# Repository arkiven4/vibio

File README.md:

This is a [Next.js](https://nextjs.org/) project bootstrapped with [`create-next-app`](https://github.com/vercel/next.js/tree/canary/packages/create-next-app).

## Build Apps

First, install necessary npm modules using command:

```sh
npm install
```

**TIPS:** In case if command failed, you can run that command again.

By default, the build target is x64 (x86_64) CPUs.
You can switch target using command (example for ARM32 chips):

```sh
sed -i 's#"nextron build -l"#"nextron build -l --armv7l"#g' package.json
```

Second, build the apps using command:

```sh
npm run build
```

**TIPS:** In case nextron main scripts is not executable, you can run this command:

```sh
chmod a+x node_modules/nextron/bin/nextron.js
```

If successfully build, you can check the image result using command:

```sh
ls -l dist/*.AppImage
```

## Run on Target Device

First, you need libfuse.so.2 to run the image.
On Arch-Linux you can install using command:

```sh
sudo pacman -S fuse2
```

then add executable to the image:

```sh
chmod a+x *.AppImage
```

Finally, you can run using command:

```sh
./*.AppImage
```

### Cleaning Builds

To clean current build and modules, you can run command:

```sh
npm ci
rm -rf dist/
rm -rf node_modules/
```

### GPIO Dev

Set Folder for GPIO file dump

```sh
export FILEDMP=/run/media/arkiven4/Project/Lab/Vibio/gpio
```

Then Start App. 

After app enter Home Page, in the `$FILEDMP` folder, there are `gpio.txt` file. it contain code that readed by app to simulate click by button.

```sh
0 -> Idle
1 -> Button 1
2 -> Button 2
3 -> Button 3
Etc...
```

For Example, When Button 1 is pressed, change value in `gpio.txt` to 1, so the app will read it and simulate click fist button / card in the app

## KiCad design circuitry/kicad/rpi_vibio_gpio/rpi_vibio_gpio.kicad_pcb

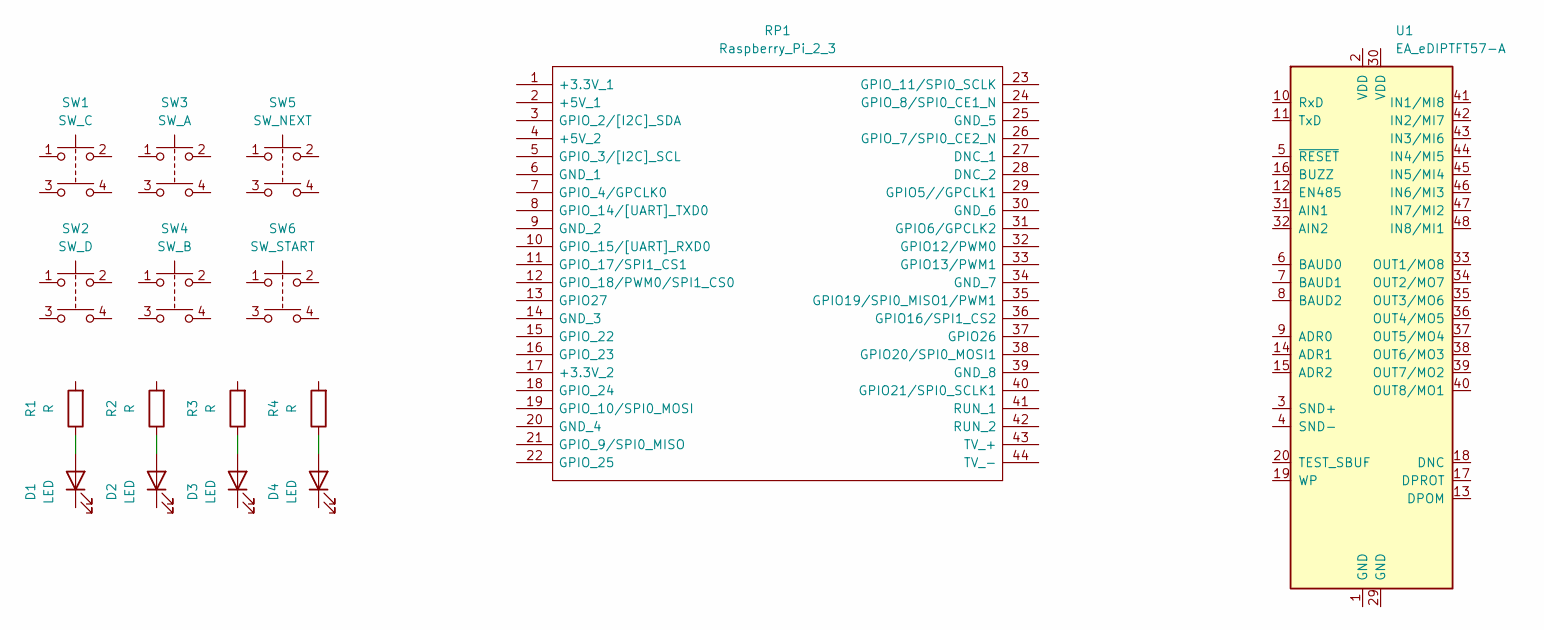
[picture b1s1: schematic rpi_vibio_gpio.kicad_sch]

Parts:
D1, D2, D3, D4: LED; LED_1206_3216Metric_Pad1.42x1.75mm_HandSolder
R1, R2, R3, R4: R; R_0805_2012Metric_Pad1.20x1.40mm_HandSolder
RP1: Raspberry_Pi_2_3; raspberrypi_2_3; Manufacturer_Part_Number Raspberry Pi 2 or 3
SW1: SW_C; SW_PUSH-12mm
SW2: SW_D; SW_PUSH-12mm
SW3: SW_A; SW_PUSH-12mm
SW4: SW_B; SW_PUSH-12mm
SW5: SW_NEXT; SW_PUSH-12mm
SW6: SW_START; SW_PUSH-12mm
U1: EA_eDIPTFT57-A; EA_eDIPTFT57-XXX

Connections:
unnamed: D1.2 (A), R1.1
unnamed: D2.2 (A), R2.1
unnamed: D3.2 (A), R3.1
unnamed: D4.2 (A), R4.1

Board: 2 copper layers, 16 parts (0 on the bottom side), 4 nets, no tracks yet.

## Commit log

2022-09-16 Initial commit from Create Next App
2022-10-03 fix vercel bug
2022-10-03 test
2022-10-03 heroku
2022-10-03 Add Localization, Add Items Data
2022-10-03 fix heroku bugs
2022-10-03 Auto Div depend on length
2022-10-03 fix json
2022-10-03 update choose game menu
2022-10-04 mengeja-gambar basic function done
2022-10-04 add note and try placeholder blur
2022-10-04 add placeholder image and fix error
2022-10-05 basic game complate
2022-10-07 update readme, and add calback after file ready
2022-10-09 Optimize Image
2022-10-09 build electron
2022-10-09 readme
2022-10-09 build for windows and arm
2022-10-09 success build app android
2022-10-10 update build sucess
2022-10-10 update readme md
2022-10-10 implement dynamic routing
2022-10-10 electron dynamic routing
2022-10-10 success electron
2022-10-10 update gitignore
2022-10-11 fix some bugs
2022-10-14 Responsivitas and add some image
2022-10-14 add Logo
2022-10-14 Akreditasi day
2022-10-14 akreditasi
2022-10-14 update bugs
2022-10-14 add gitignore
2022-10-14 some change
2022-10-14 remove subtitle
2022-10-14 add bg sound
2022-10-15 sync with main
2022-10-17 full screen and hide menu window
2022-10-19 Readme enhancement
2022-10-19 auto updater boilerplate
2022-10-19 Fix Some typos
2022-10-19 Some Readme
2022-10-19 fix log bugs
2022-10-19 Cleaning builds
2022-10-20 if file exist click button
2022-10-20 window width
2022-10-21 fix responsive issue in raspberry, add modoal
2022-10-21 Sync Fix Raspberry Issue
2022-10-21 fix issue modal
2022-10-21 remove unwanted file
2022-10-22 add auto updater
2022-10-22 some adjustment
2022-10-22 1.0.3
2022-10-22 1.0.4
2022-10-22 fix eslint and update gitnore
2022-10-22 1.0.5
2022-10-22 update some autoupdate bugs
2022-10-22 update note
2022-10-22 1.0.6
2022-10-22 fix update issue
2022-10-22 1.0.7
2022-10-22 1.0.8
2022-10-22 1.0.9
2022-10-22 fix bugs auto update
2022-10-22 Change version
2022-10-22 1.0.10
2022-10-22 add GPIO and home button
2022-10-22 sync with nextron
2022-10-24 Some Dumb Hardware Design
2022-10-24 Docs on Current Dev
2022-10-24 fix offline mode
2022-10-30 idk update
2022-10-30 idk part 2
2022-10-30 add speech recognition
2022-11-03 speech recognition ok
2022-12-27 demoNpetunjuk
2022-12-27 fix error
2022-12-27 fix bugs
2022-12-27 disable music at petunjuk
2023-02-17 add data and other but stil error
2023-02-20 update items
2023-02-20 update category
2023-02-21 add item and add Permainan Listening
2023-03-23 Monev_1
2023-04-02 Before Monev
2023-04-02 3x dengarkan gambar
2023-09-10 update some folder, update capacitor
2023-09-12 add buffering data and add google asr natve
2023-09-13 add slider and add virtual keyboard
2023-09-13 add sayuran and fix some change
2023-09-13 apply mengeja gambar dev
2023-09-13 fix some display bugs
2023-09-13 add logout and fix buffer data
2023-09-19 add sayuran
2023-09-19 update script
2023-11-02 update some bugs
